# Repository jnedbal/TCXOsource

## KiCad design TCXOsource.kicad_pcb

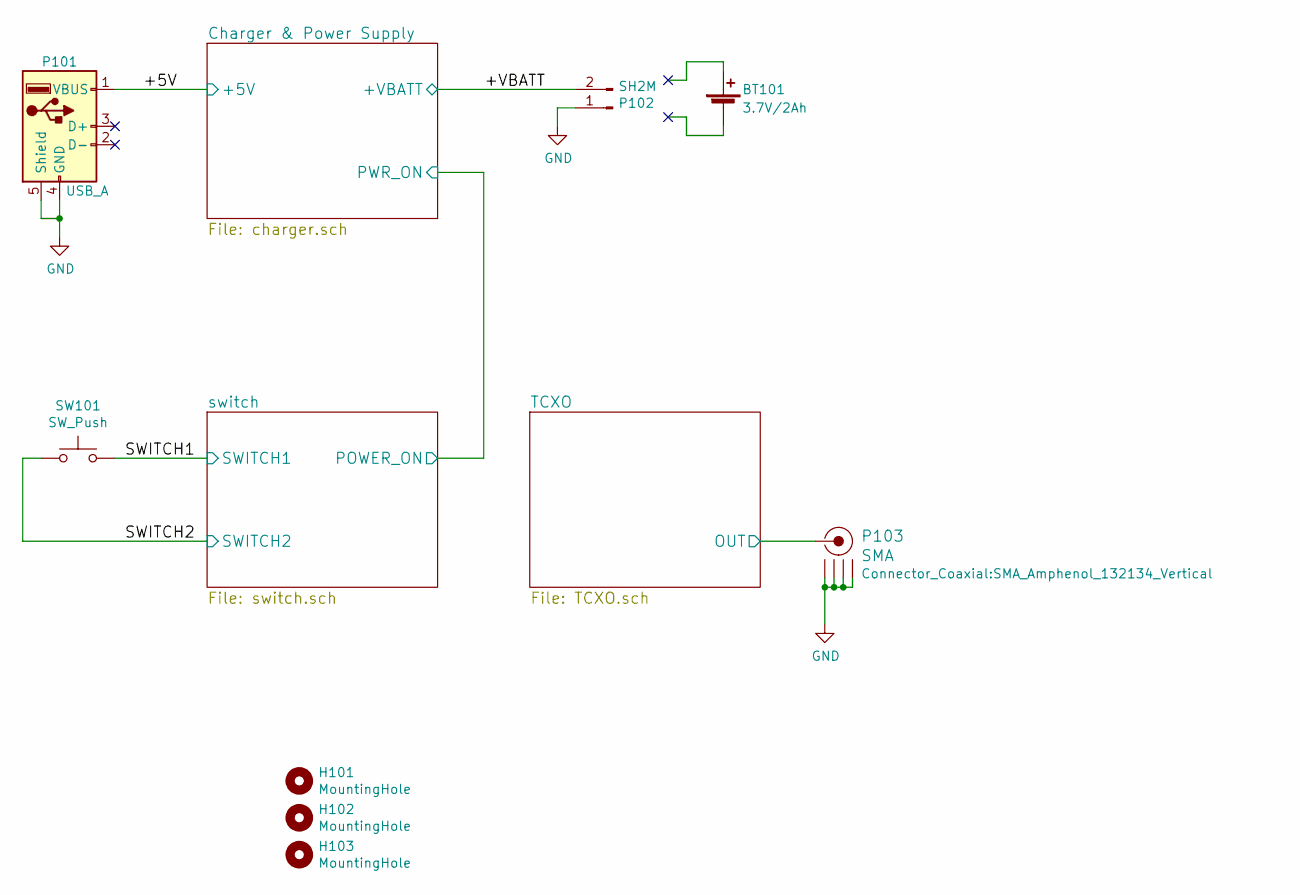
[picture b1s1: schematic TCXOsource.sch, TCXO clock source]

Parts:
BT101: 3.7V/2Ah; MIKROE-1120; Part Number MIKROE-1120
H101, H102, H103: MountingHole; MountingHole_3.2mm_M3
P101: USB_A; Molex_USB_A; Part Number 48037-0001
P102: SH2M; JST_XH_S2B-XH-A_1x02_P2.50mm_Horizontal; Part Number S2B-XH-A(LF)(SN)
P103: SMA; SMA_Amphenol_132134_Vertical; Part Number 73251-2200
SW101: SW_Push; SW_PUSH_6mm_H13mm; Part Number 2-1825910-7

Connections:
+5V: P101.1 (VBUS); also elsewhere on the board
+BATT: P102.2; also elsewhere on the board
/SWITCH1: SW101.2; also elsewhere on the board
/SWITCH2: SW101.1; also elsewhere on the board
/TCXO/OUT: P103.1 (RF); also elsewhere on the board
GND: P101.4 (GND), P101.5 (Shield), P102.1, P103.2 (GND1), P103.3 (GND2), P103.4 (GND3), P103.5 (GND4); also elsewhere on the board

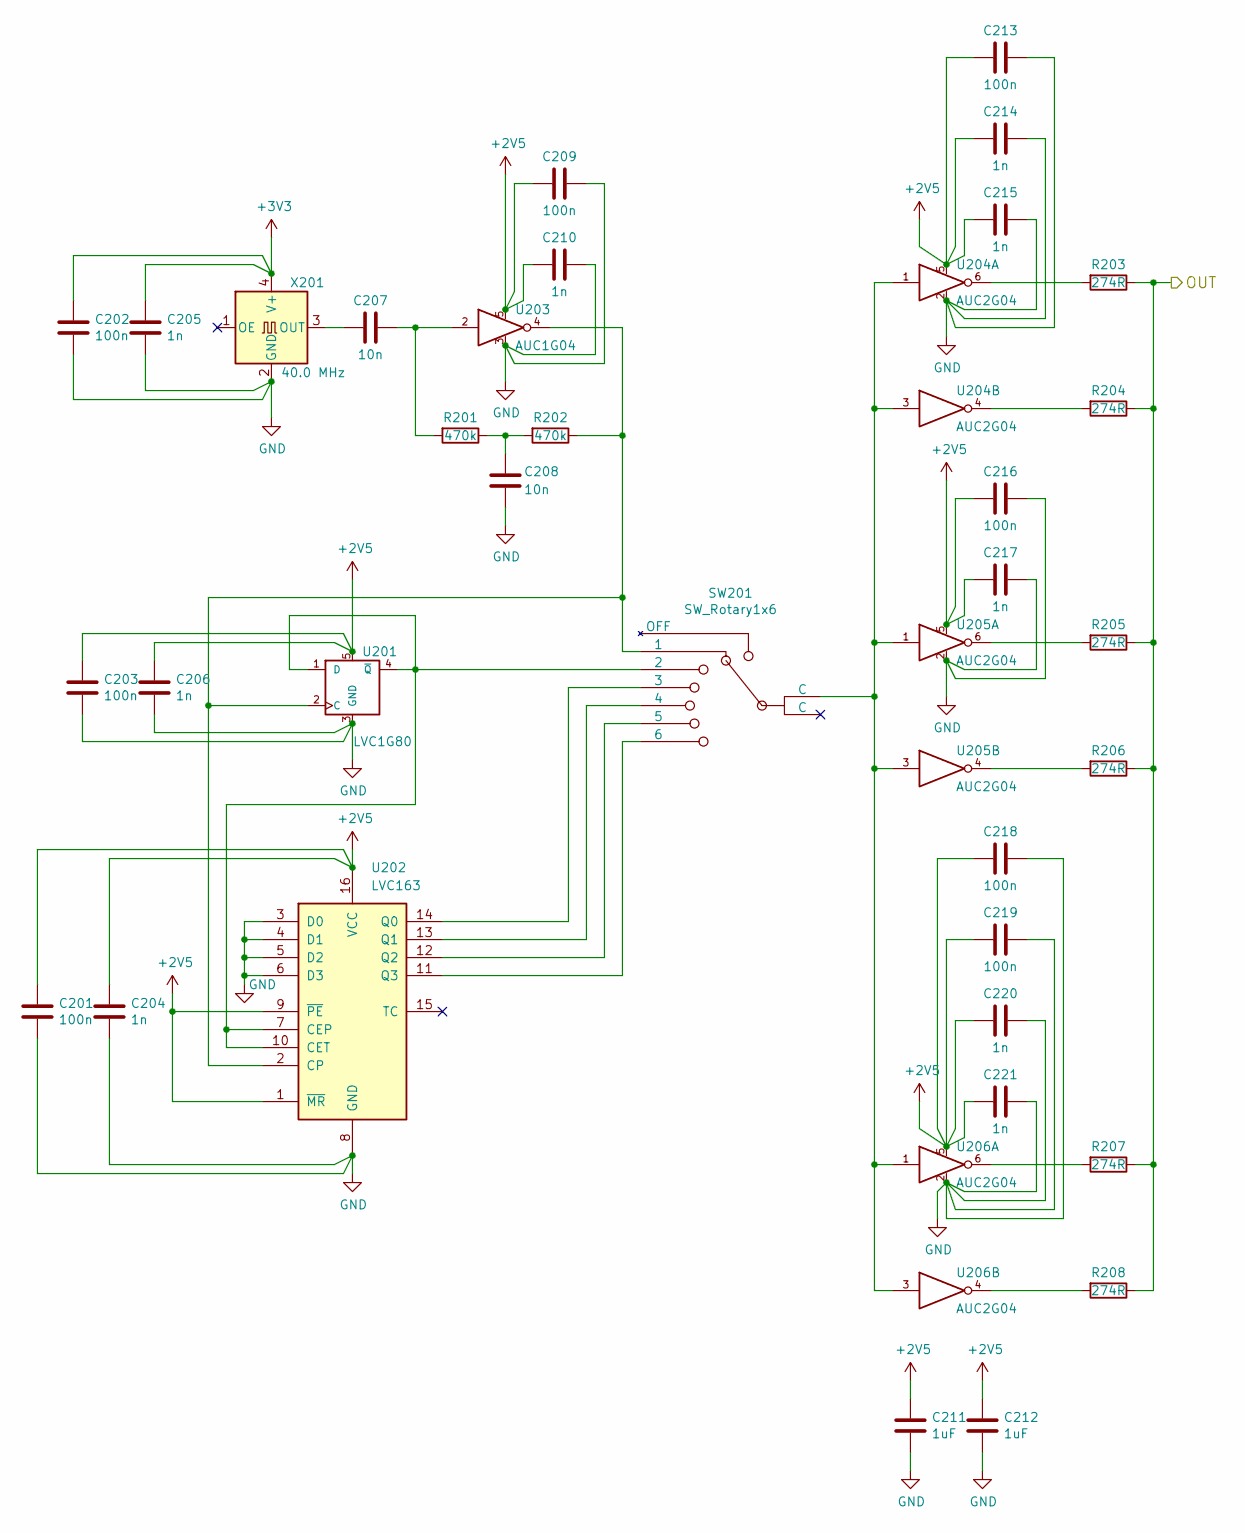
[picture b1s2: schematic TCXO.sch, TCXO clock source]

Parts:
C201, C202, C203, C209, C213, C216, C218, C219: 100n; C_0603_1608Metric; Part Number MC0603B104K500
C204, C205, C206, C210, C214, C215, C217, C220, C221: 1n; C_0402_1005Metric; Part Number GRM1555C1H102JA01D
C207, C208: 10n; C_0603_1608Metric; Part Number MCU0603R103KCT
C211, C212: 1uF; C_0603_1608Metric; Part Number CGA3E1X7R1C105M080AC
R201, R202: 470k; R_0603_1608Metric; Part Number MCMR06X4703FTL
R203, R204, R205, R206, R207, R208: 274R; R_0402_1005Metric; Part Number MCMR04X2740FTL
SW201: SW_Rotary1x6; Nidec_Copal_SS-10-16; Part Number SS-10-16NP-LE
U201: LVC1G80; TSOP-5_1.65x3.05mm_P0.95mm; Part Number 74LVC1G80GV,125
U202: LVC163; TSSOP-16_4.4x5mm_P0.65mm; Part Number 74LVC163PW,118
U203: AUC1G04; SOT-353_SC-70-5_Handsoldering; Part Number SN74AUC1G04DCKR
U204: AUC2G04; SOT-363_SC-70-6_Handsoldering
U205, U206: AUC2G04; SOT-363_SC-70-6_Handsoldering; Part Number SN74AUC2G04DCKR
X201: 40.0 MHz; Oscillator_SMD_EuroQuartz_XO32-4Pin_3.2x2.5mm_HandSoldering; Part Number I537-2P3-40.0000MHZ

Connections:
+2V5: C201.2, C203.2, C204.2, C206.2, C209.2, C210.1, C211.1, C212.1, C213.2, C214.1, C215.1, C216.2, C217.1, C218.2, C219.2, C220.1, C221.1, U201.5, U202.1 (~MR), U202.9 (~PE), U202.16 (VCC), U203.5, U204.5, U205.5, U206.5; also elsewhere on the board
+3V3: C202.2, C205.2, X201.4 (V+); also elsewhere on the board
/TCXO/OUT: R203.1, R204.1, R205.1, R206.1, R207.1, R208.1; also elsewhere on the board
GND: C201.1, C202.1, C203.1, C204.1, C205.1, C206.1, C208.2, C209.1, C210.2, C211.2, C212.2, C213.1, C214.2, C215.2, C216.1, C217.2, C218.1, C219.1, C220.2, C221.2, U201.3 (GND), U202.3 (D0), U202.4 (D1), U202.5 (D2), U202.6 (D3), U202.8 (GND), U203.3, U204.2, U205.2, U206.2, X201.2 (GND); also elsewhere on the board
unnamed: C207.1, R201.2, U203.2
unnamed: C207.2, X201.3 (OUT)
unnamed: C208.1, R201.1, R202.2
unnamed: R202.1, SW201.1, U201.2 (C), U202.2 (CP), U203.4
unnamed: R203.2, U204.6
unnamed: R204.2, U204.4
unnamed: R205.2, U205.6
unnamed: R206.2, U205.4
unnamed: R207.2, U206.6
unnamed: R208.2, U206.4
unnamed: SW201.3 (2), U201.1 (D), U201.4 (~Q), U202.7 (CEP), U202.10 (CET)
unnamed: SW201.4 (3), U202.14 (Q0)
unnamed: SW201.5 (4), U202.13 (Q1)
unnamed: SW201.6 (5), U202.12 (Q2)
unnamed: SW201.7 (C), U204.1, U204.3, U205.1, U205.3, U206.1, U206.3
unnamed: SW201.8 (6), U202.11 (Q3)

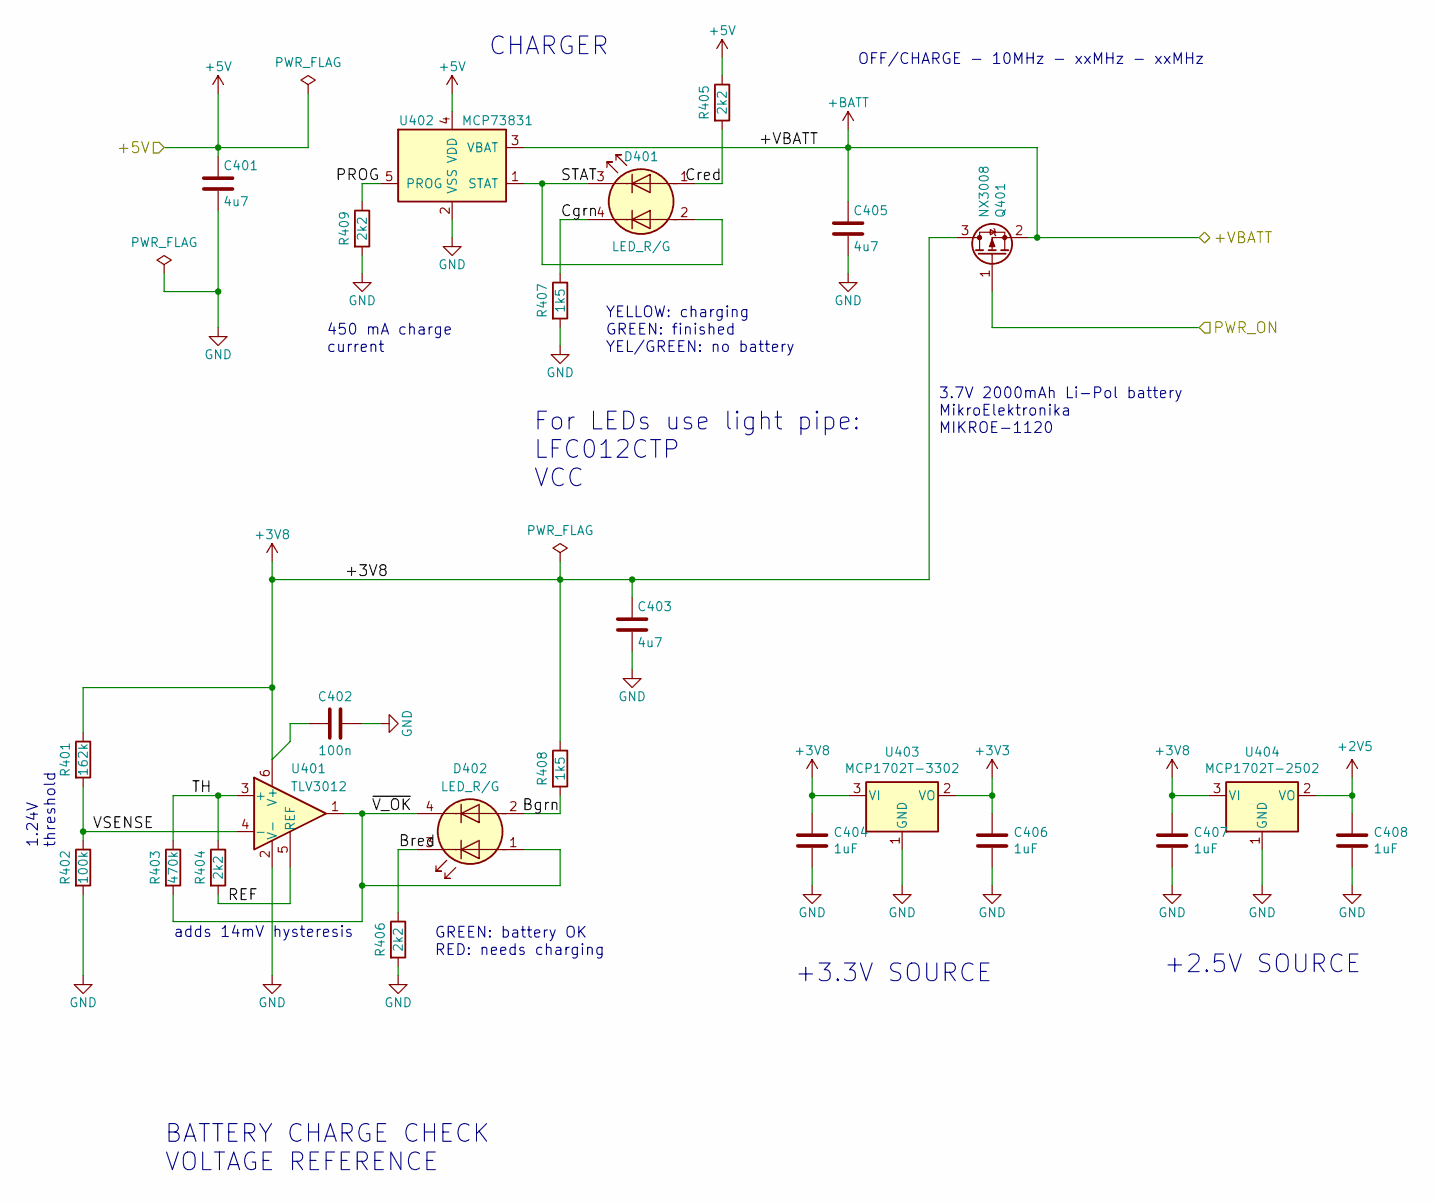
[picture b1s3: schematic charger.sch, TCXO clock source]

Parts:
C401, C403, C405: 4u7; C_0603_1608Metric; Part Number EMK107ABJ475KA-T
C402: 100n; C_0603_1608Metric; Part Number MC0603B104K500
C404, C406, C407, C408: 1uF; C_0603_1608Metric; Part Number CGA3E1X7R1C105M080AC
D401, D402: LED_R/G; LEDdual_3.2x2.8; Part Number 150141RV73100
Q401: NX3008; SOT-23; Part Number NX3008PBK,215
R401: 162k; R_0603_1608Metric; Part Number CRCW0603162KFKEA
R402: 100k; R_0603_1608Metric; Part Number MCWR06X1003FTL
R403: 470k; R_0603_1608Metric; Part Number MCMR06X4703FTL
R404, R405, R406, R409: 2k2; R_0603_1608Metric; Part Number MCWR06X2201FTL
R407, R408: 1k5; R_0603_1608Metric; Part Number MCWR06X1501FTL
U401: TLV3012; SOT-23-6; Part Number TLV3012AIDBVR
U402: MCP73831; SOT-23-5; Part Number MCP73831T-2DCI/OT
U403: MCP1702T-3302; SOT-23; Part Number MCP1702T-3302E/CB
U404: MCP1702T-2502; SOT-23; Part Number MCP1702T-2502E/CB

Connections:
+2V5: C408.1, U404.2 (VO); also elsewhere on the board
+3V3: C406.1, U403.2 (VO); also elsewhere on the board
+3V8: C402.2, C403.1, C404.1, C407.1, Q401.3 (D), R401.1, R408.1, U401.6 (V+), U403.3 (VI), U404.3 (VI)
+5V: C401.1, R405.1, U402.4 (VDD); also elsewhere on the board
+BATT: C405.1, Q401.2 (S), U402.3 (VBAT); also elsewhere on the board
/Charger & Power Supply/Bgrn: D402.2 (A2), R408.2
/Charger & Power Supply/Bred: D402.3 (K1), R406.1
/Charger & Power Supply/Cgrn: D401.4 (K2), R407.1
/Charger & Power Supply/Cred: D401.1 (A1), R405.2
/Charger & Power Supply/PROG: R409.1, U402.5 (PROG)
/Charger & Power Supply/REF: R404.2, U401.5 (REF)
/Charger & Power Supply/STAT: D401.2 (A2), D401.3 (K1), U402.1 (STAT)
/Charger & Power Supply/TH: R403.1, R404.1, U401.3 (+)
/Charger & Power Supply/VSENSE: R401.2, R402.1, U401.4 (-)
/Charger & Power Supply/~V_OK: D402.1 (A1), D402.4 (K2), R403.2, U401.1
/switch/POWER_ON: Q401.1 (G); also elsewhere on the board
GND: C401.2, C402.1, C403.2, C404.2, C405.2, C406.2, C407.2, C408.2, R402.2, R406.2, R407.2, R409.2, U401.2 (V-), U402.2 (VSS), U403.1 (GND), U404.1 (GND); also elsewhere on the board

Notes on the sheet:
adds 14mV hysteresis
1.24V threshold
3.7V 2000mAh Li-Pol battery MikroElektronika MIKROE-1120
450 mA charge current
OFF/CHARGE - 10MHz - xxMHz - xxMHz
YELLOW: charging GREEN: finished YEL/GREEN: no battery
GREEN: battery OK RED: needs charging
CHARGER
BATTERY CHARGE CHECK VOLTAGE REFERENCE
+3.3V SOURCE
For LEDs use light pipe: LFC012CTP VCC
+2.5V SOURCE

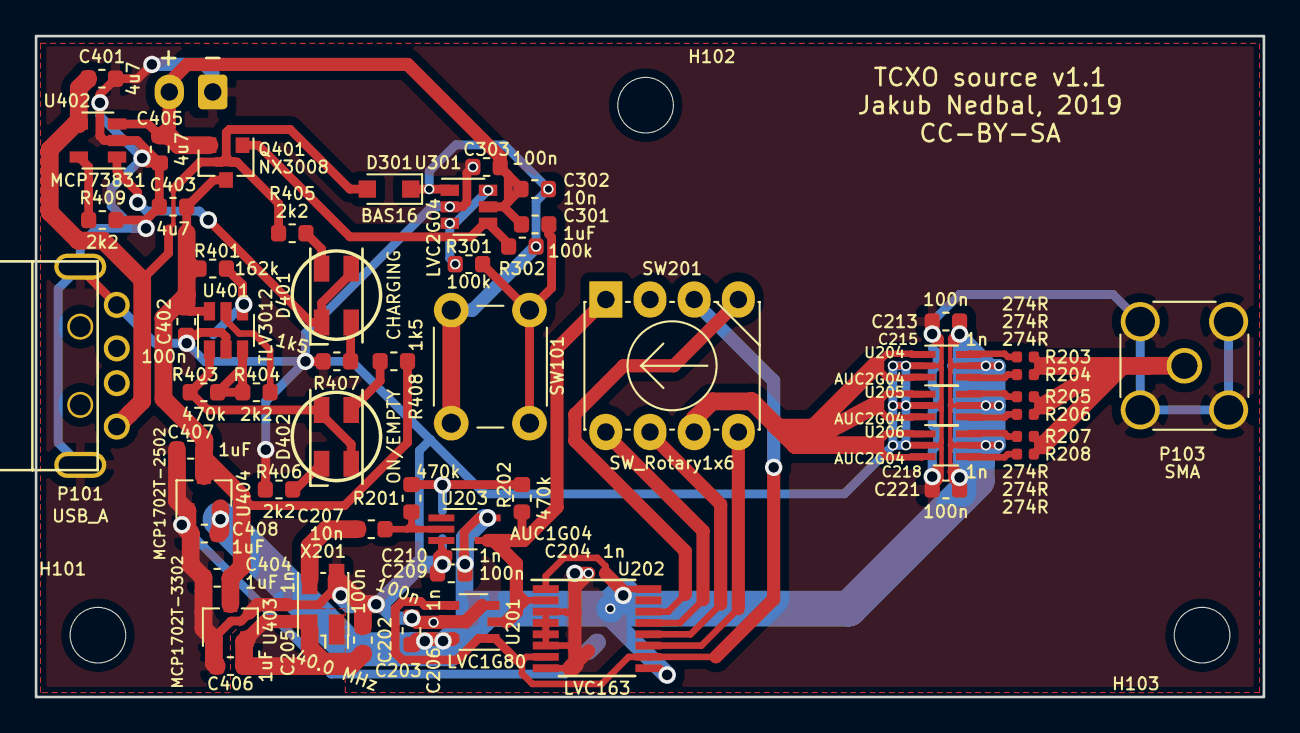
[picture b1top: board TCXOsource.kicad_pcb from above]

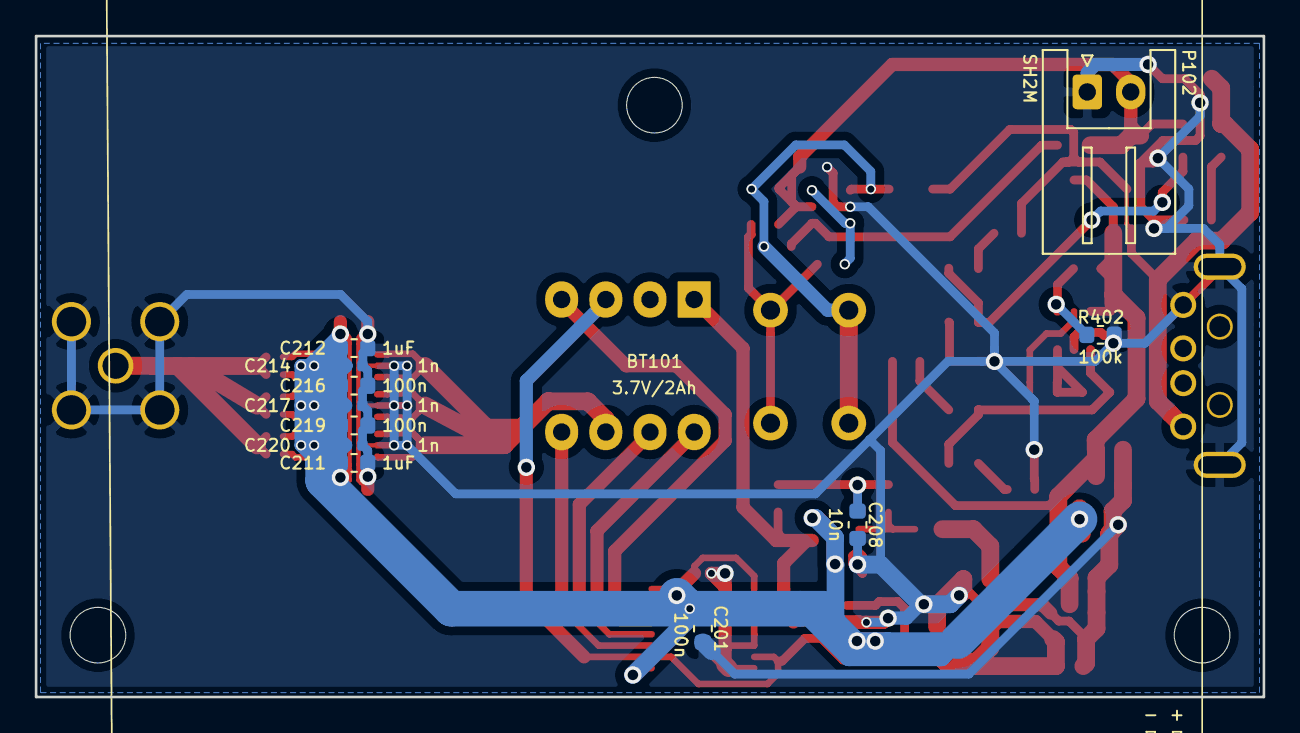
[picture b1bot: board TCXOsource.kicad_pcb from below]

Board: 2 copper layers, 70.6 x 38.0 mm, 76 parts (12 on the bottom side), 37 nets.

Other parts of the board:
C301: 1uF; C_0603_1608Metric
C302: 10n; C_0603_1608Metric
C303: 100n; C_0603_1608Metric
D301: BAS16; D_SOD-323_HandSoldering
R301, R302: 100k; R_0603_1608Metric
U301: LVC2G04; SOT-23-6

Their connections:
+5V: D301.2; also elsewhere on the board
+BATT: C301.1, C302.1, C303.2, U301.5; also elsewhere on the board
/SWITCH1: C301.2, R301.2; also elsewhere on the board
/SWITCH2: C302.2, D301.1, R302.2, U301.1; also elsewhere on the board
/switch/POWER_ON: R302.1, U301.4; also elsewhere on the board
GND: C303.1, U301.2; also elsewhere on the board
unnamed: R301.1, U301.3, U301.6

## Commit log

2019-06-16 Initial commit. Sent for manufacture.
2019-07-16 Updated several part details with alternative suppliers
2019-08-14 Changed output resistor from 300R to 274R to consider the impedance of the inverter output driver.

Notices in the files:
TCXO.sch:
CC-BY-SA
